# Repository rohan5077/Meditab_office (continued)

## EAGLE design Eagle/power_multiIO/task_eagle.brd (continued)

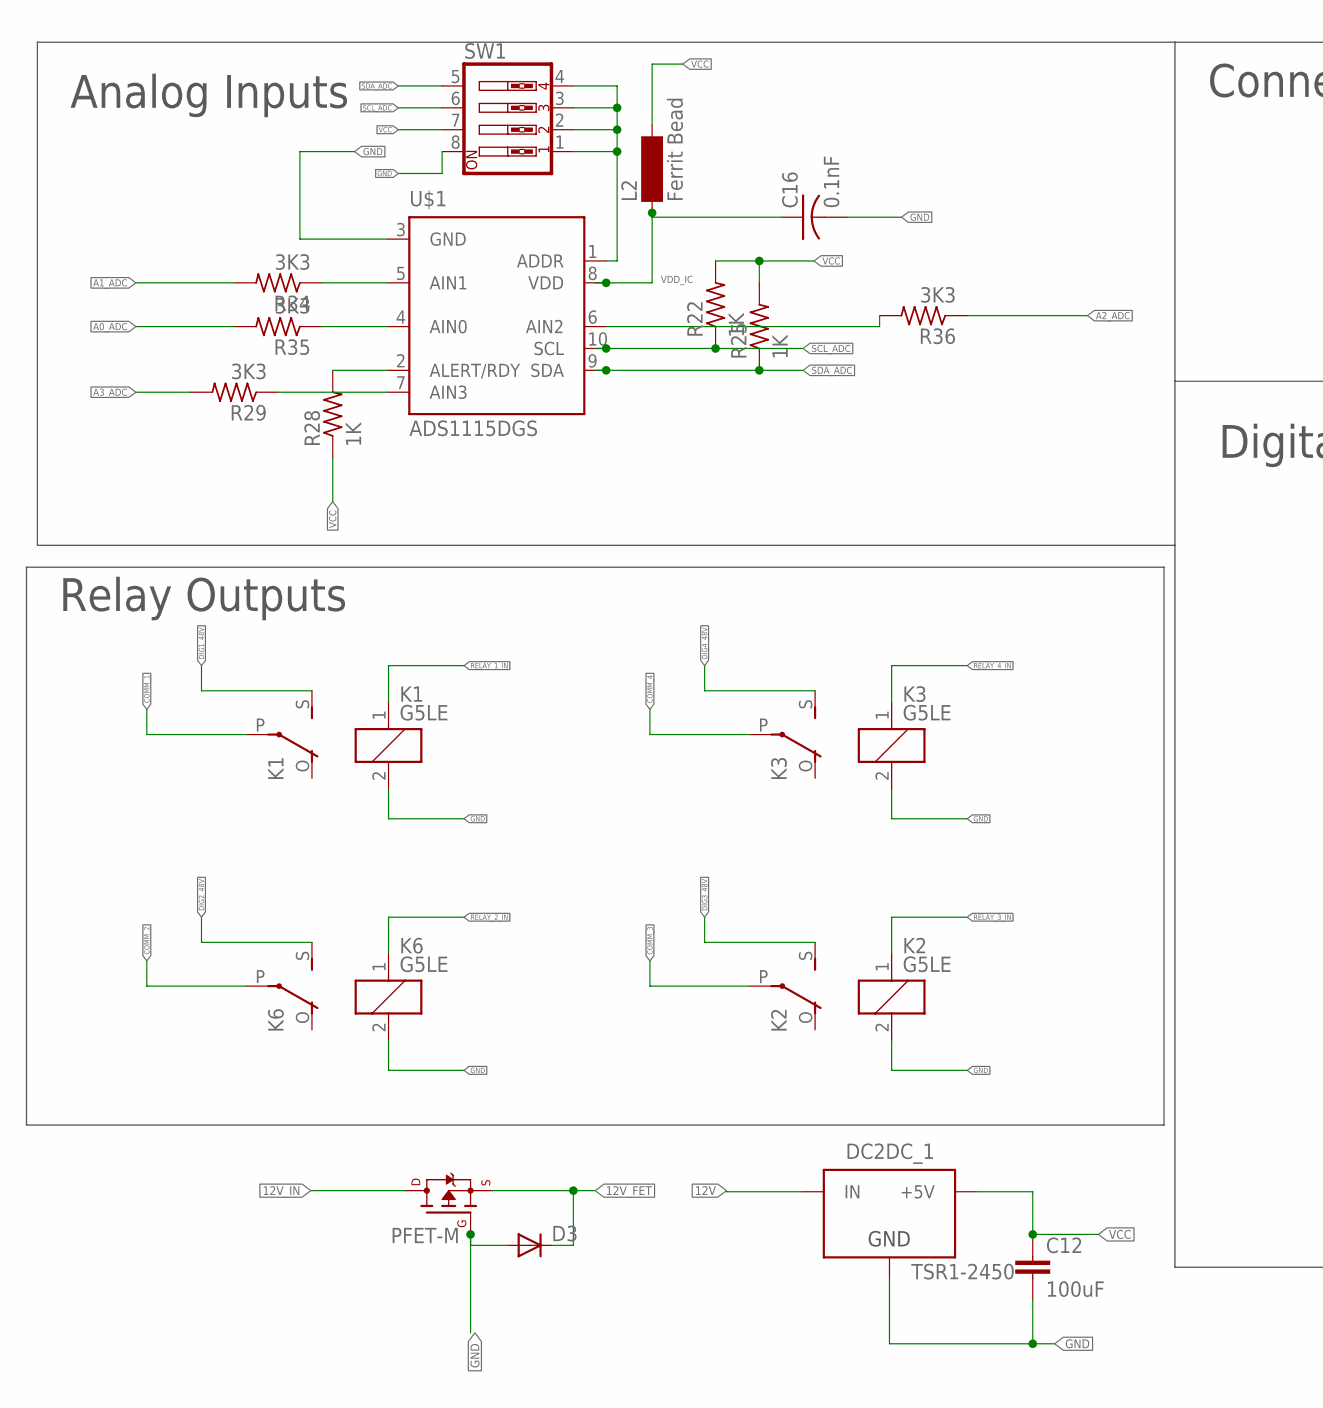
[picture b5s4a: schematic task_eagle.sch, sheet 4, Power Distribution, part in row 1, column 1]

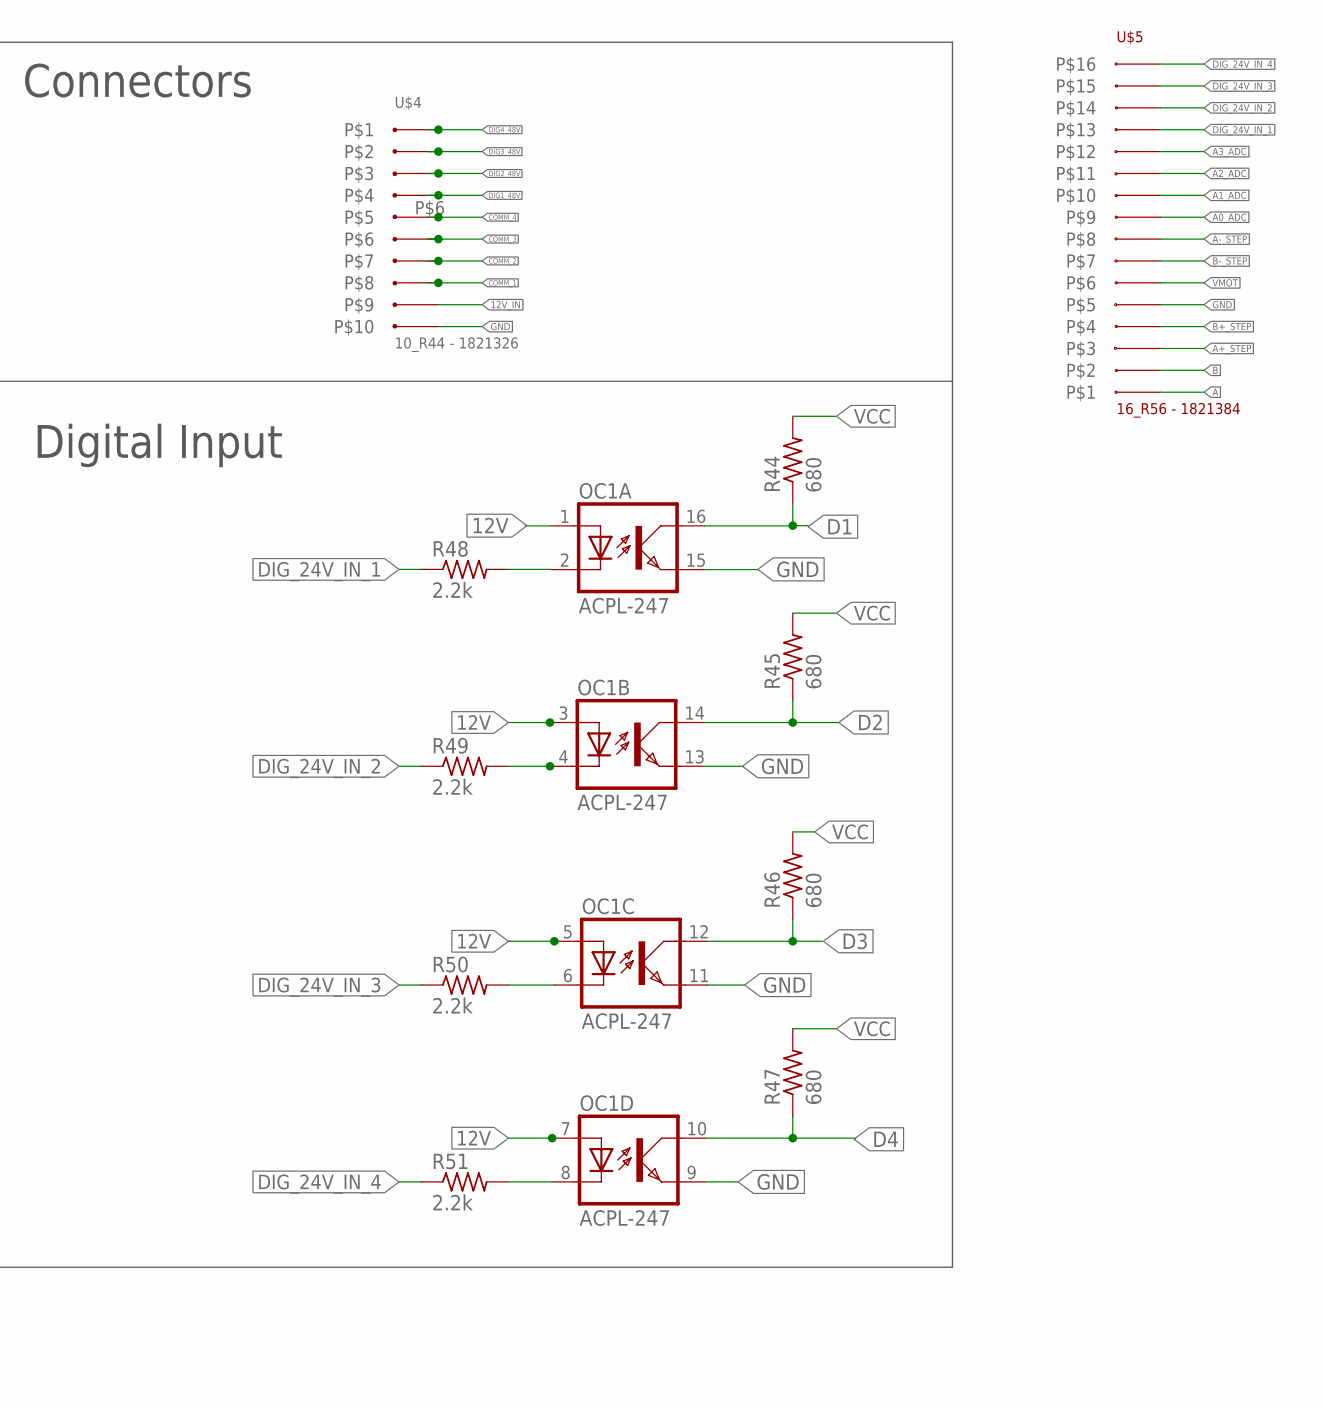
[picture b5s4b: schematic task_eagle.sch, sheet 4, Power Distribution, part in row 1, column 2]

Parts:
C12: 100uF; C0603
C16: 0.1nF; C0603
D3: DIODE-MINIMELF; MINIMELF
DC2DC_1: TSR1-2450; TSR-1
K1, K2, K3, K6: G5LE
L2: Ferrit Bead; SM-1206
OC1: ACPL-247; SOP16
PFET-M: FQP47P06NORMAL; FQP47P06-NORMAL
R22, R25, R28: 1K; R0603
R29, R34, R35, R36: 3K3; R0603
R44, R45, R46, R47: 680; R0603
R48, R49, R50, R51: 2.2k; R0603
SW1: SW_DIP-4; EDG-04
U$1: ADS1115DGS; MSOP10
U$4: 10_R44 - 1821326
U$5: 16_R56 - 1821384

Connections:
12V: DC2DC_1.1 (IN), OC1.1 (A), OC1.3 (A), OC1.5 (A), OC1.7 (A); also elsewhere on the board
12V_FET: D3.C, PFET-M.3 (S); also elsewhere on the board
12V_IN: PFET-M.2 (D), U$4.P$10
A: U$5.P$1; also elsewhere on the board
A0_ADC: R35.2, U$5.P$9
A1_ADC: R34.2, U$5.P$10
A2_ADC: R36.1, U$5.P$11
A3_ADC: R29.2, U$5.P$12
A+_STEP: U$5.P$3; also elsewhere on the board
A-_STEP: U$5.P$8; also elsewhere on the board
B: U$5.P$2; also elsewhere on the board
B+_STEP: U$5.P$4; also elsewhere on the board
B-_STEP: U$5.P$7; also elsewhere on the board
COMM_1: K1.P, U$4.P$9
COMM_2: K6.P, U$4.P$8
COMM_3: K2.P, U$4.P$7
COMM_4: K3.P, U$4.P$6
D1: OC1.16 (COL), R44.1; also elsewhere on the board
D2: OC1.14 (COL), R45.1; also elsewhere on the board
D3: OC1.12 (COL), R46.1; also elsewhere on the board
D4: OC1.10 (COL), R47.1; also elsewhere on the board
DIG1_48V: K1.S, U$4.P$5
DIG2_48V: K6.S, U$4.P$4
DIG3_48V: K2.S, U$4.P$3
DIG4_48V: K3.S, U$4.P$2
DIG_24V_IN_1: R48.1, U$5.P$13
DIG_24V_IN_2: R49.1, U$5.P$14
DIG_24V_IN_3: R50.1, U$5.P$15
DIG_24V_IN_4: R51.1, U$5.P$16
GND: C12.2, C16.2, D3.A, DC2DC_1.2 (GND), K1.2, K2.2, K3.2, K6.2, OC1.9 (EMIT), OC1.11 (EMIT), OC1.13 (EMIT), OC1.15 (EMIT), PFET-M.1 (G), SW1.8, U$1.3 (GND), U$4.P$11, U$5.P$5; also elsewhere on the board
unnamed: SW1.1, SW1.2, SW1.3, SW1.4, U$1.1 (ADDR)
unnamed: R34.1, U$1.5 (AIN1)
unnamed: R35.1, U$1.4 (AIN0)
unnamed: R29.1, U$1.7 (AIN3)
unnamed: R28.2, U$1.2 (ALERT/RDY)
unnamed: R36.2, U$1.6 (AIN2)
unnamed: OC1.4 (C), R49.2
unnamed: OC1.8 (C), R51.2
unnamed: OC1.6 (C), R50.2
unnamed: OC1.2 (C), R48.2
RELAY_1_IN: K1.1; also elsewhere on the board
RELAY_2_IN: K6.1; also elsewhere on the board
RELAY_3_IN: K2.1; also elsewhere on the board
RELAY_4_IN: K3.1; also elsewhere on the board
SCL_ADC: R22.1, SW1.6, U$1.10 (SCL); also elsewhere on the board
SDA_ADC: R25.1, SW1.5, U$1.9 (SDA); also elsewhere on the board
VCC: C12.1, DC2DC_1.3 (+5V), L2.2, R22.2, R25.2, R28.1, R44.2, R45.2, R46.2, R47.2, SW1.7; also elsewhere on the board
VDD_IC: C16.1, L2.1, U$1.8 (VDD)
VMOT: U$5.P$6; also elsewhere on the board

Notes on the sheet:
Analog Inputs
Relay Outputs
Connectors
Digital Input

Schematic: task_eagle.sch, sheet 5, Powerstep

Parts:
U$2: POWERSTEP01-SHIELD; POWERSTEP1

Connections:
3.3V: U$2.3.3V, U$2.IOREF (3.3V); also elsewhere on the board
A+_STEP: U$2.A+; also elsewhere on the board
A-_STEP: U$2.A-; also elsewhere on the board
B+_STEP: U$2.B+; also elsewhere on the board
B-_STEP: U$2.B-; also elsewhere on the board
CCW: U$2.SW; also elsewhere on the board
CS_M: U$2.A2-CS (A2/CS); also elsewhere on the board
GND: U$2.GND@0 (GND), U$2.GND@1 (GND), U$2.GND@2 (GND), U$2.GND@3 (GND); also elsewhere on the board
MISO_1: U$2.D12-MISO (D12/MISO); also elsewhere on the board
MOSI_1: U$2.D11-MOSI (D11/MOSI); also elsewhere on the board
RESET_1: U$2.D8-RESET (D8/RESET); also elsewhere on the board
SCK_1: U$2.D13-SCK (D13/SCK); also elsewhere on the board
VMOT: U$2.VS+ (VMOT); also elsewhere on the board

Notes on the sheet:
Powerstep

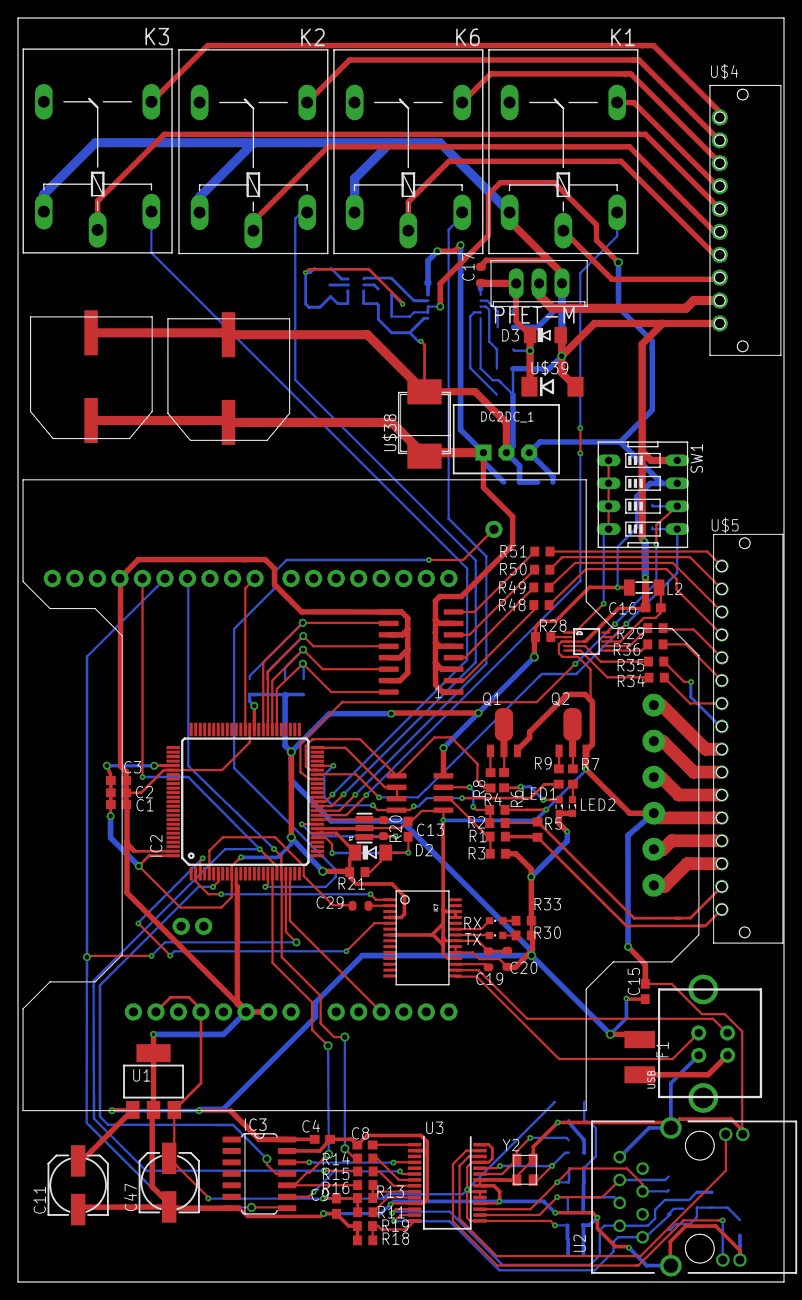
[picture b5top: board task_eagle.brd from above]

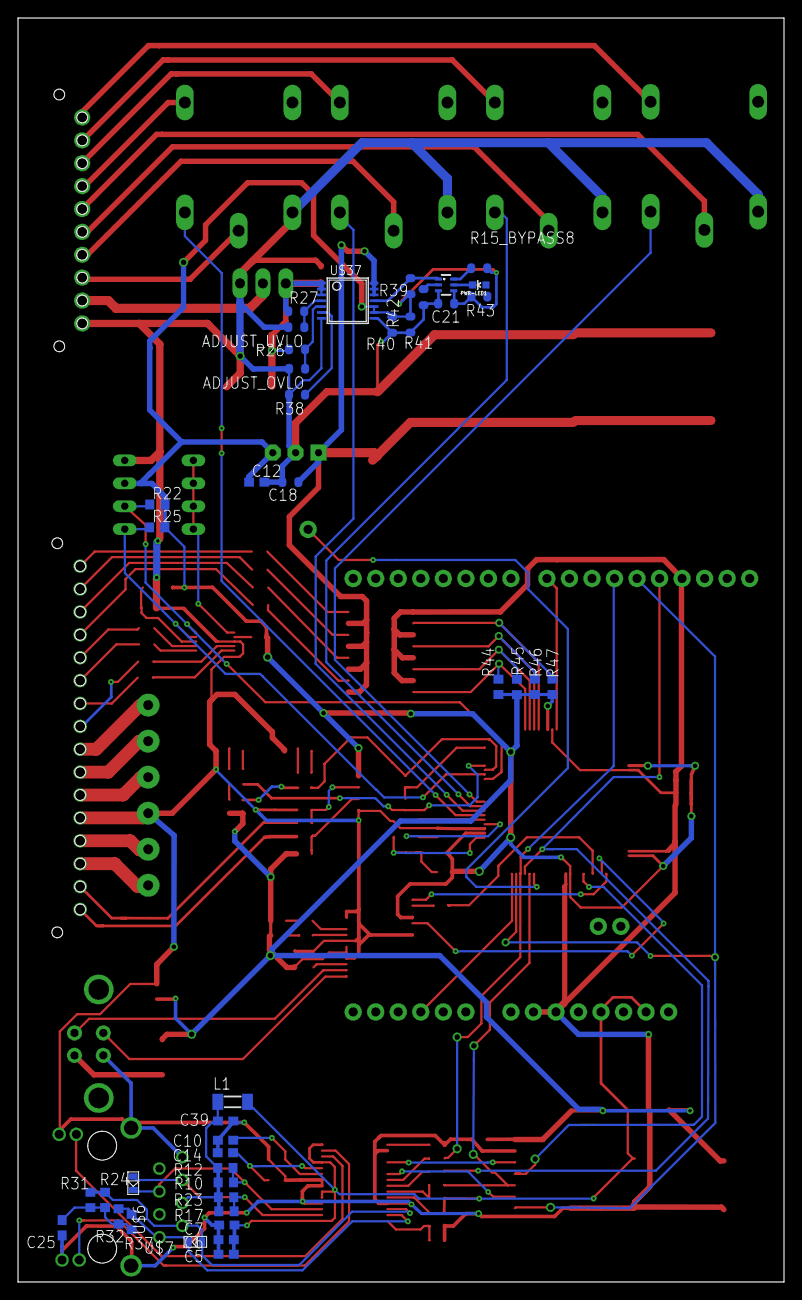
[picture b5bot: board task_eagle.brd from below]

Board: 2 copper layers, 85.0 x 140.3 mm, 121 parts (41 on the bottom side), 110 nets.
